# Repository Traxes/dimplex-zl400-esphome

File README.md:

# Dimplex ZL 400 VF – ESPHome controller for Home Assistant

**English** · [Deutsch](README.de.md)

> [!TIP]
> **Want a ready-made one?** I can build the assembled PCB and the 3D-printed enclosure for you – **in any color**, and the case can be adapted to your installation (shape, mounting, cable exits). If you're interested, **[open a request](https://github.com/Traxes/dimplex-zl400-esphome/issues/new?title=Request%3A%20ready-made%20controller&body=Hi%21%20I%20am%20interested%20in%20a%20ready-made%20controller%20%28assembled%20PCB%20%2B%203D-printed%20enclosure%29.%0A%0A-%20Quantity%3A%0A-%20Enclosure%20color%3A%0A-%20Changes%20to%20the%20enclosure%20%28optional%29%3A%0A-%20Shipping%20country%3A%0A%0A%28Please%20do%20not%20post%20your%20address%20or%20phone%20number%20here%20%E2%80%93%20details%20are%20arranged%20privately.%29)**. Please don't post your address or phone number in the issue – details are arranged privately.

<p align="center">
  
  &nbsp;
  
</p>
<p align="center"><sub>Left: installed on a ZL 400 VF, wires to the unit's terminal board. Right: controller v3 in the printed case (lid removed).</sub></p>

A drop-in replacement for the wall control panel (“Bedienelement Typ 1”) of **Dimplex ZL 300 VF / ZL 400 VF** home ventilation units. A Seeed **XIAO ESP32-C6** reads the unit's five 24 V status outputs through optocouplers and “presses” the up/down buttons with optocoupler-driven PNP switches. In Home Assistant the unit shows up as a normal fan with three speeds.

**Highlights**

- Galvanically isolated: the ESP is powered only by USB-C, nothing but optocouplers crosses to the unit's 24 V side.
- Closed-loop control: every key press is verified through the unit's LED outputs; retries with back-off, fault entities for HA.
- KiCad 10 project + ready-to-order JLCPCB files (Gerber, BOM, CPL).
- Snap-fit 3D-printed enclosure without screws, generated by a parametric Fusion 360 script.
- Worst-case analysis, SPICE Monte Carlo and FMEA in [`docs/qa`](docs/qa) (German).

**Status (2026-10-19):** installed and running in a ZL 400 VF. Live test off → 1 → 3 → 2 → off: LED feedback within 3 s for every step, no fault flags.

> [!WARNING]
> The ventilation unit contains mains voltage (230 V). Read the **[safety notes](#safety)** before you open the unit or connect anything. Build at your own risk. This is not a Dimplex product.

## Contents

| Folder | What's inside |
|---|---|
| [`hardware/controller-v3`](hardware/controller-v3) | KiCad project, schematic PDF, JLCPCB fabrication files |
| [`hardware/emulator-lab-v2`](hardware/emulator-lab-v2) | Bench emulator of the unit's terminal board (not built/tested yet) |
| [`firmware`](firmware) | ESPHome config `trax_ha_c6.yaml`, `secrets.example.yaml` |
| [`gehaeuse`](gehaeuse) | Enclosure: STL, 3MF, Bambu Studio project, STEP, Fusion 360 script |
| [`docs`](docs) | QA reports, interactive commissioning checklist, images, dimension sheet |
| [`tools`](tools) | Python scripts used for QA, simulation and fabrication checks |

## Safety

> [!CAUTION]
> Working on the ventilation unit can be **life-threatening**: there is mains voltage (230 V) inside. Read this section completely before you start.

**Electrical**

- Before opening the unit or the terminal compartment, disconnect it from mains **on all poles** (circuit breaker or isolating switch). Secure it against being switched back on and verify that it is dead. Work on mains wiring is for qualified electricians only.
- The controller is designed **only for the unit's 24 V DC control circuit** (PCB3 terminals `+`, `−`, `AUS_x`, `EIN_x`).
  - Never connect any terminal to mains or to another voltage source.
  - The absolute maximum is 30 V; above 27.5 V parts run outside their derating limits.
- Measure `+` to `−` on PCB3 (DC volts) and check every wire against the [wiring diagram](#wiring) before you connect the controller. Swapping `+` and `−` is blocked by diodes; other wiring mistakes are not.
- Use **ferrules** on stranded wires, strip only as much as the terminal needs, and pull-test every wire. A stray strand can short the unit's 24 V supply.
- Leave all other PCB3 terminals untouched. In particular, keep the **RM (smoke detector) bridge** in place: it is a safety shutdown input of the unit.
- Do not connect other loads to the unit's 24 V supply. Its transformer is only rated for a few control panels and sensors (Dimplex manual, table 4.1).

**ESP / USB side**

- Power the XIAO only from a **certified USB power supply** (safety extra-low voltage, CE marked). Never feed it from the unit's 24 V.
- Never connect USB ground or any ESP pin to the unit's wiring. The isolation between the two sides must stay intact.

**Enclosure and location**

- The printed enclosure is **not flame-retardant**: PLA and PETG are not UL 94 V-0. The controller dissipates only milliwatts, but keep it away from heat sources and out of the air stream of electric heater coils.
- PLA softens from about 55 °C; use PETG or ASA for warm locations.
- Install only in dry, frost-free rooms (the same requirements as for the unit itself): no condensation, no outdoor use.
- Close the lid before operation; it protects the terminals against accidental contact.

**Ventilation function**

- Home ventilation protects the building against moisture and mould. Make sure your automations **can never keep the unit off for long periods**, and keep the minimum ventilation required for your building (in Germany, for example, the moisture-protection level of DIN 1946-6).
- If a **fireplace or other combustion appliance** shares the air volume, the safety devices required for that combination (for example a pressure monitor) stay mandatory. This controller does not replace them, and remote control must never override them.
- The unit's own protective functions (frost protection, smoke-detector shutdown, filter alarm) stay active. Do not bypass them.
- A Wi-Fi or firmware fault can leave the unit at its last stage. Watch `control_failed` and `feedback_lost` in Home Assistant; the unit's own display and buttons keep working as a fallback.

**Liability**

- Building and using this is at your own risk. Connecting third-party electronics may affect the warranty of the ventilation unit. The documents come without any guarantee of correctness. This project is not affiliated with Dimplex.

## How it works

| Direction | Circuit |
|---|---|
| Unit → ESP (AUS0–AUS4) | +24 V → 10 kΩ → EL817 LED → AUS. The unit switches AUS to 0 V, exactly like the LEDs of the original panel (≈ 2 mA). Output side: 3.3 V → GPIO with 10 kΩ pull-down. |
| ESP → unit (EIN0/EIN1) | GPIO → 330 Ω → EL817 → pulls the base of an MMBT3906 (22 kΩ); the PNP puts +24 V on EIN through 1 kΩ – like pressing the panel button. 300 ms pulses. |
| Power | ESP from USB-C only (an ESP powered from the unit's 24 V had tripped error E05 at power-up). 24 V side: 1N4148W reverse-polarity protection in + and −, “24V OK” LED. Load on the unit ≈ 1–10 mA. |

## Wiring

Set the unit to **service menu 20 → 21 Bedienelement → “Typ1”**. Terminal assignment follows the Dimplex installation manual ZL 300/400 VF, chapter 4.5.4, fig. 4.13 ([PDF](https://www.dimplex.eu/sites/g/files/emiian586/files/media_import/medias/docus/5/Dimplex_ZL300VF_Montageanweisung-WP_DE_FD9910.pdf)).

> [!IMPORTANT]
> Unlike the original panel, this controller needs the **GND → “−”** wire. Measure between PCB3 “+” and “−” first: the design is rated for 21.6–27 V (see [Known limitations](#known-limitations)).

## Build it

### 1. PCB

1. Upload `hardware/controller-v3/fertigung-jlcpcb/gerbers.zip` to JLCPCB (2 layers, 1.6 mm, 75 × 64 mm), choose PCBA Economic and add the BOM and CPL files. Q1/Q2 (SOT-23) rotation is already corrected by 180° in the CPL. Still check the placement preview.
2. Hand-solder a Seeed **XIAO ESP32-C6** and 5.08 mm screw terminals (2-pin J1, 5-pin J2, 2-pin J3). The XIAO can be soldered directly (the enclosure is dimensioned for that) or plugged into 1×7 socket headers.
3. Commission it step by step with [`docs/Inbetriebnahme_Controller_v3.html`](docs/Inbetriebnahme_Controller_v3.html) (download and open locally; it covers measuring points, multimeter settings and expected values; German).

| Part (assembled by JLCPCB) | LCSC | Qty | Refs |
|---|---|---|---|
| 1N4148W SOD-123 | C81598 | 7 | D1–D5, D7, D8 |
| LED green 0805 | C2297 | 1 | D6 |
| MMBT3906 SOT-23 | C2143 | 2 | Q1, Q2 |
| EL817S SMD-4 | C63268 | 7 | U1–U7 |
| 10 kΩ 0805 | C17414 | 14 | R1–R10, R15, R16, R18, R19 |
| 22 kΩ 0805 | C17560 | 3 | R13, R14, R17 |
| 330 Ω 0805 | C17630 | 2 | R11, R12 |
| 1 kΩ 0805 | C17513 | 2 | R20, R21 |

### 2. Firmware

1. Copy `firmware/secrets.example.yaml` to `secrets.yaml` and fill it in. Never commit it, it is in `.gitignore`.
2. Add `trax_ha_c6.yaml` in the ESPHome dashboard and flash it over USB. If you get “Failed to connect”, hold the **B (BOOT)** button next to the USB socket while plugging in the cable. After that, OTA works.
3. Adopt the device in Home Assistant (ESPHome integration).

| Entity | Purpose |
|---|---|
| `fan.<device>_ventilation` | 3 speeds: 33 / 66 / 100 %, off = unit off |
| `sensor.<device>_ventilation_level` | Actual stage 0–3 from the unit's LEDs |
| `sensor.<device>_ventilation_status` | OK / adjusting / fault text |
| `binary_sensor.<device>_ventilation_auto`, `…_error` | Auto mode, fault/filter LED |
| `…_control_failed`, `…_feedback_lost`, `…_stuck_key_suspected` | Diagnostics |
| `sensor.<device>_ventilation_uncommanded_changes` | Stage changes not caused by HA |
| `button.<device>_ventilation_clear_faults` | Reset diagnostics |

#### In Home Assistant

<p align="center"><sub>Device page with the fan dialog. The activity log shows a real command from an automation: fan on at 22:10:00, LED feedback for stage 1 in the same second, status “OK” at 22:10:02.</sub></p>

- The fan dialog offers **Off / Low / Medium / High**: stages 0–3, 0 / 33 / 66 / 100 %.
- The status sensor uses German texts:

| Status | Meaning |
|---|---|
| `OK` | Idle, stage confirmed by the unit's LEDs |
| `Stellt ein: 1 → 2` | Adjusting from stage 1 to 2 |
| `Aus (oder 24 V fehlt)` | Unit is off – or there is no 24 V / no LED signal at all |
| `Gestört/unbekannt – keine Rückmeldung` | A key press caused no LED change (check 24 V, wiring, EIN) |
| `Steuerung fehlgeschlagen` | Target not reached after all retries |
| `Verdacht Dauerdruck – Hardware prüfen (T2)` | Stage moved against the pressed direction – possible stuck key |
| `Start` | Booting; key presses are blocked until the first sync |

Tested with ESPHome 2026.9.1 on a XIAO ESP32-C6.

**Control logic:** A requested speed becomes single key presses (300 ms pulse, 700 ms pause). After each press the firmware waits up to 2 s for the stage LEDs to change. If they don't, it retries with back-off (1/2/4/4 s, max. 10 presses). On boot the entity syncs to the real stage without pressing anything.

```yaml
# Example automation action
action: fan.set_percentage
target:
  entity_id: fan.trax_ha_c6_ventilation
data:
  percentage: 66   # 33 = stage 1, 66 = stage 2, 100 = stage 3; use fan.turn_off for off
```

LED feedback is immediate. The fans themselves need about 30–70 s to reach their speed.

### 3. Enclosure

- **Size:** 80.7 × 69.8 × 24.1 mm, 95.8 mm long including the two wall-mounting tabs (slots for Ø 4 screws).
- **No hardware needed:** pins on the bosses locate the PCB, four hold-downs in the lid clamp it, and the lid snaps into four windows. To open it, push each hook inwards through its window with a small screwdriver.
- **Openings:** nine labelled wire holes (Ø 3.9 mm, aligned with the terminal entries), a USB-C opening, pin holes for RESET/BOOT (paper clip) and a light pipe for “24V OK”.
- **Printing** (tested on a Bambu Lab P2S, PLA): 0.2 mm layers, 4 walls, 4 bottom layers, 15 % infill, no supports, lid printed top-down. About 1 h 25 min and 49 g. Use PETG for warm locations.
- **Files:**
  - `CentralVentilationCase_BambuStudio_P2S_PLA.3mf`: ready-to-print Bambu Studio project
  - `…_Geometrie.3mf`: for other slicers
  - single STL files
  - STEP assembly with a PCB dummy
- **Modify:** [`gehaeuse/fusion/gehaeuse_fusion.py`](gehaeuse/fusion/gehaeuse_fusion.py) rebuilds the whole model in Fusion 360 via the API. All dimensions are at the top of the script; the measurements come from the [dimension sheet](docs/bilder/massblatt_controller_v3.png).

## Emulator (optional)

Bench replica of the unit's terminal board: DIP switches pull AUS0–4 to 0 V, LEDs show EIN0/EIN1. **Not manufactured or tested yet.** LED polarities in the assembly preview are unverified.

## Known limitations

Details are in [`docs/qa/QA_Verifikation_2026-10-15.md`](docs/qa/QA_Verifikation_2026-10-15.md) (German).

- **Supply voltage:** designed to EEE-INST-002 derating for 21.6–30 V. Above **27.5 V** the output optocouplers U6/U7 exceed the derating limit (absolute max 35 V), and above ≈ 29 V so do R1–R5. Spikes on the 24 V line have not been measured.
- **EIN input current** of the unit has not been measured. It decides whether R20/R21 = 1 kΩ is optimal (up to 4 mA the unit still sees ≥ 19 V).
- **Short circuit on EIN** is tolerable for the pulse length only: a permanent short would put 0.5 W into R20/R21, which are rated 0.125 W.
- **A stuck key is not single-fault safe:** a shorted Q1/Q2 or U6/U7 would hold a button down. The firmware only detects it indirectly (`stuck_key_suspected`).

## Tools

`tools/qa` and `tools/verifikation` contain the scripts that generated and verified schematic and layout:
- KiCad 10 Python
- ngspice via the KiCad DLL
- gerbonara / shapely

Local paths are replaced by `<PROJEKT>` / `<HOME>`; adjust them before running.

## License

[MIT](LICENSE): free to use, build, modify and share, also commercially, as long as the license notice is kept. Symbols and footprints embedded in the KiCad files come from the KiCad libraries (CC-BY-SA 4.0 with the KiCad design exception) and do not restrict your own boards.

## Disclaimer

Dimplex and ZL 400 VF are trademarks of Glen Dimplex Deutschland GmbH; XIAO is a trademark of Seeed Studio. This project is not affiliated with or endorsed by either company.

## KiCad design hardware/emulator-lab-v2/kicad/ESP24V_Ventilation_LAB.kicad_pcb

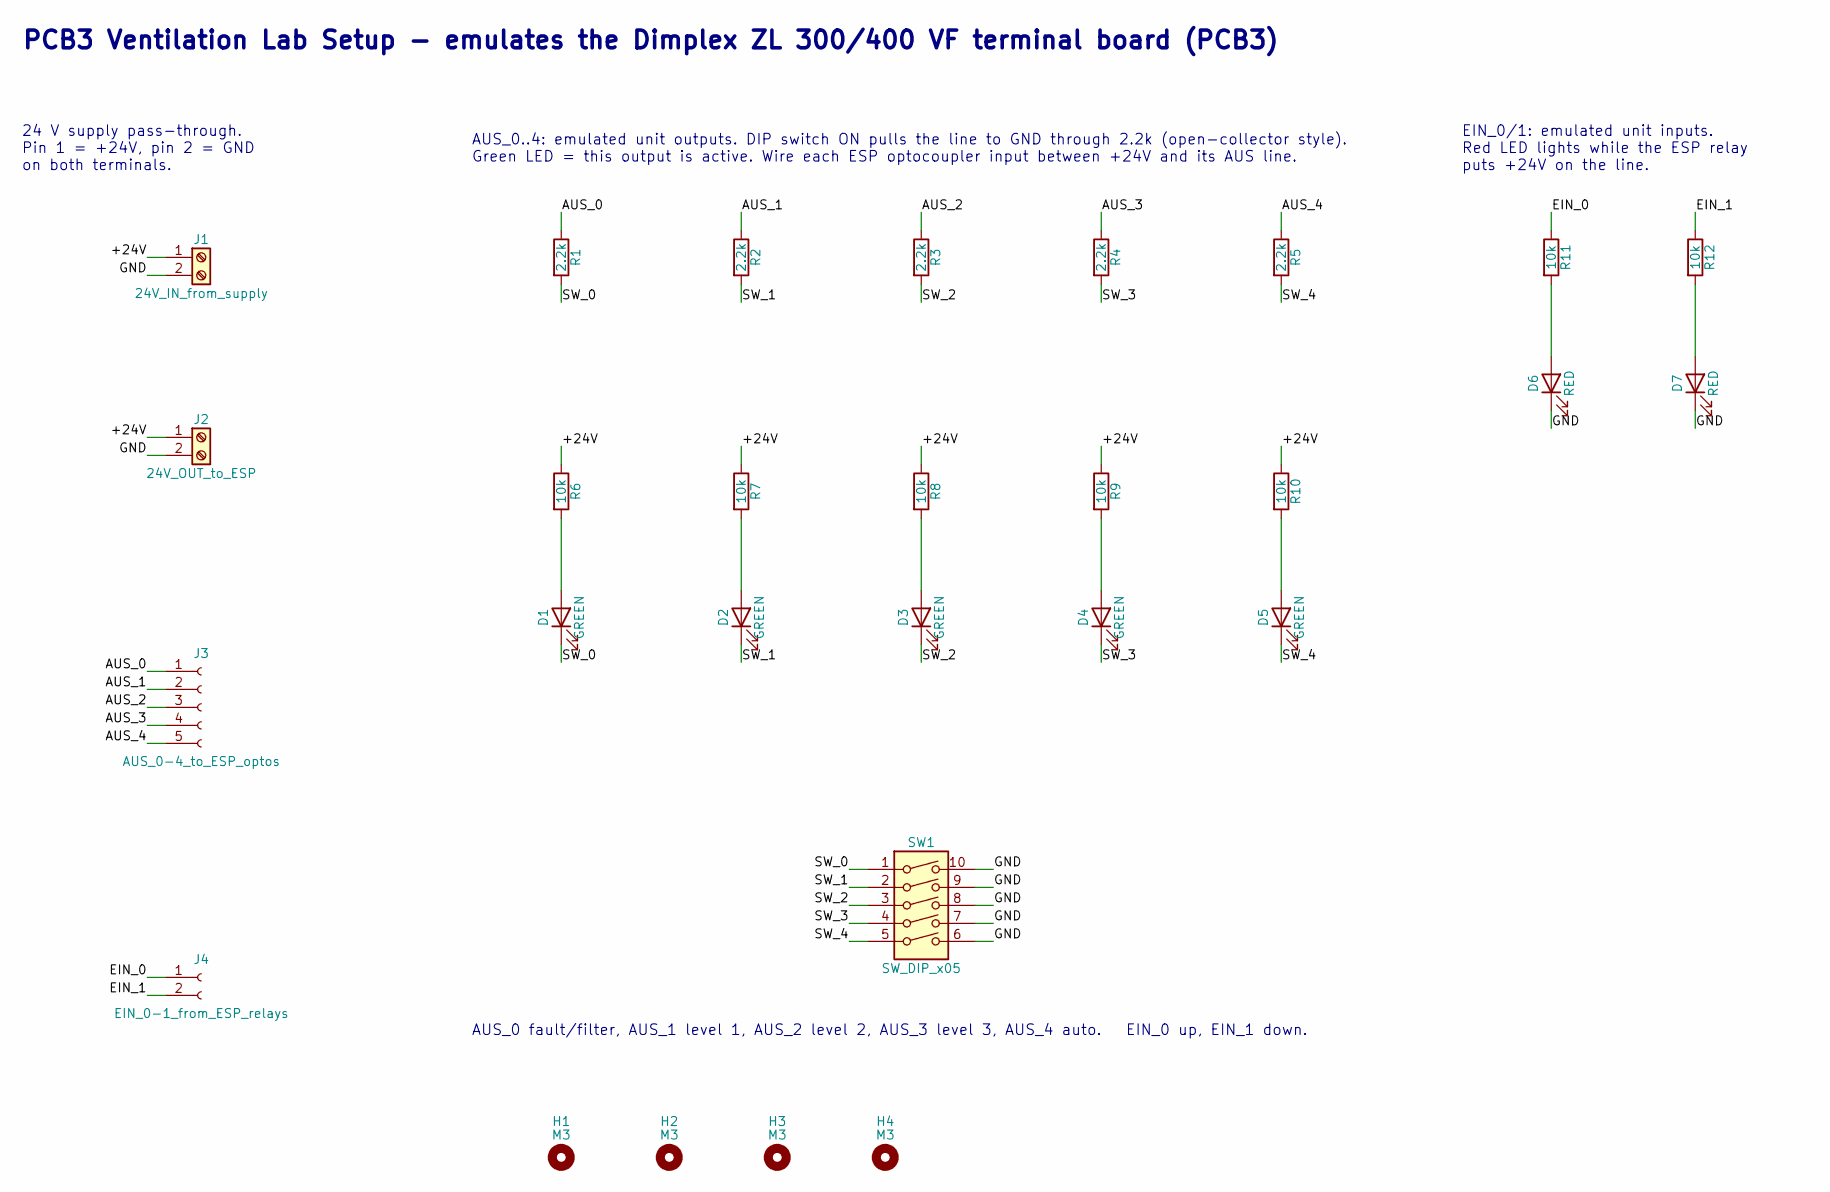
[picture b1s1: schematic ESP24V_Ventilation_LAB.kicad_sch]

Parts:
D1, D2, D3, D4, D5: GREEN; LED_0805_2012Metric; LCSC C2297
D6, D7: RED; LED_0805_2012Metric; LCSC C84256
H1, H2, H3, H4: M3; MountingHole_3.2mm_M3
J1: 24V_IN_from_supply; TerminalBlock_Phoenix_MKDS-1,5-2-5.08_1x02_P5.08mm_Horizont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
J2: 24V_OUT_to_ESP; TerminalBlock_Phoenix_MKDS-1,5-2-5.08_1x02_P5.08mm_Horizont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
J3: AUS_0-4_to_ESP_optos; PinSocket_1x05_P2.54mm_Vertical
J4: EIN_0-1_from_ESP_relays; PinSocket_1x02_P2.54mm_Vertical
R1, R2, R3, R4, R5: 2.2k; R_0805_2012Metric; LCSC C17520
R6, R7, R8, R9, R10, R11, R12: 10k; R_0805_2012Metric; LCSC C17414
SW1: SW_DIP_x05; SW_DIP_SPSTx05_Slide_9.78x14.88mm_W7.62mm_P2.54mm

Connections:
/+24V: J1.1, J2.1, R6.1, R7.1, R8.1, R9.1, R10.1
/AUS_0: J3.1, R1.1
/AUS_1: J3.2, R2.1
/AUS_2: J3.3, R3.1
/AUS_3: J3.4, R4.1
/AUS_4: J3.5, R5.1
/EIN_0: J4.1, R11.1
/EIN_1: J4.2, R12.1
/GND: D6.1 (K), D7.1 (K), J1.2, J2.2, SW1.6, SW1.7, SW1.8, SW1.9, SW1.10
/SW_0: D1.1 (K), R1.2, SW1.1
/SW_1: D2.1 (K), R2.2, SW1.2
/SW_2: D3.1 (K), R3.2, SW1.3
/SW_3: D4.1 (K), R4.2, SW1.4
/SW_4: D5.1 (K), R5.2, SW1.5
unnamed: D1.2 (A), R6.2
unnamed: D2.2 (A), R7.2
unnamed: D3.2 (A), R8.2
unnamed: D4.2 (A), R9.2
unnamed: D5.2 (A), R10.2
unnamed: D6.2 (A), R11.2
unnamed: D7.2 (A), R12.2

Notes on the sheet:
PCB3 Ventilation Lab Setup - emulates the Dimplex ZL 300/400 VF terminal board (PCB3)
AUS_0..4: emulated unit outputs. DIP switch ON pulls the line to GND through 2.2k (open-collector style). Green LED = this output is active. Wire each ESP optocoupler input between +24V and its AUS line.
EIN_0/1: emulated unit inputs. Red LED lights while the ESP relay puts +24V on the line.
AUS_0 fault/filter, AUS_1 level 1, AUS_2 level 2, AUS_3 level 3, AUS_4 auto. EIN_0 up, EIN_1 down.
24 V supply pass-through. Pin 1 = +24V, pin 2 = GND on both terminals.

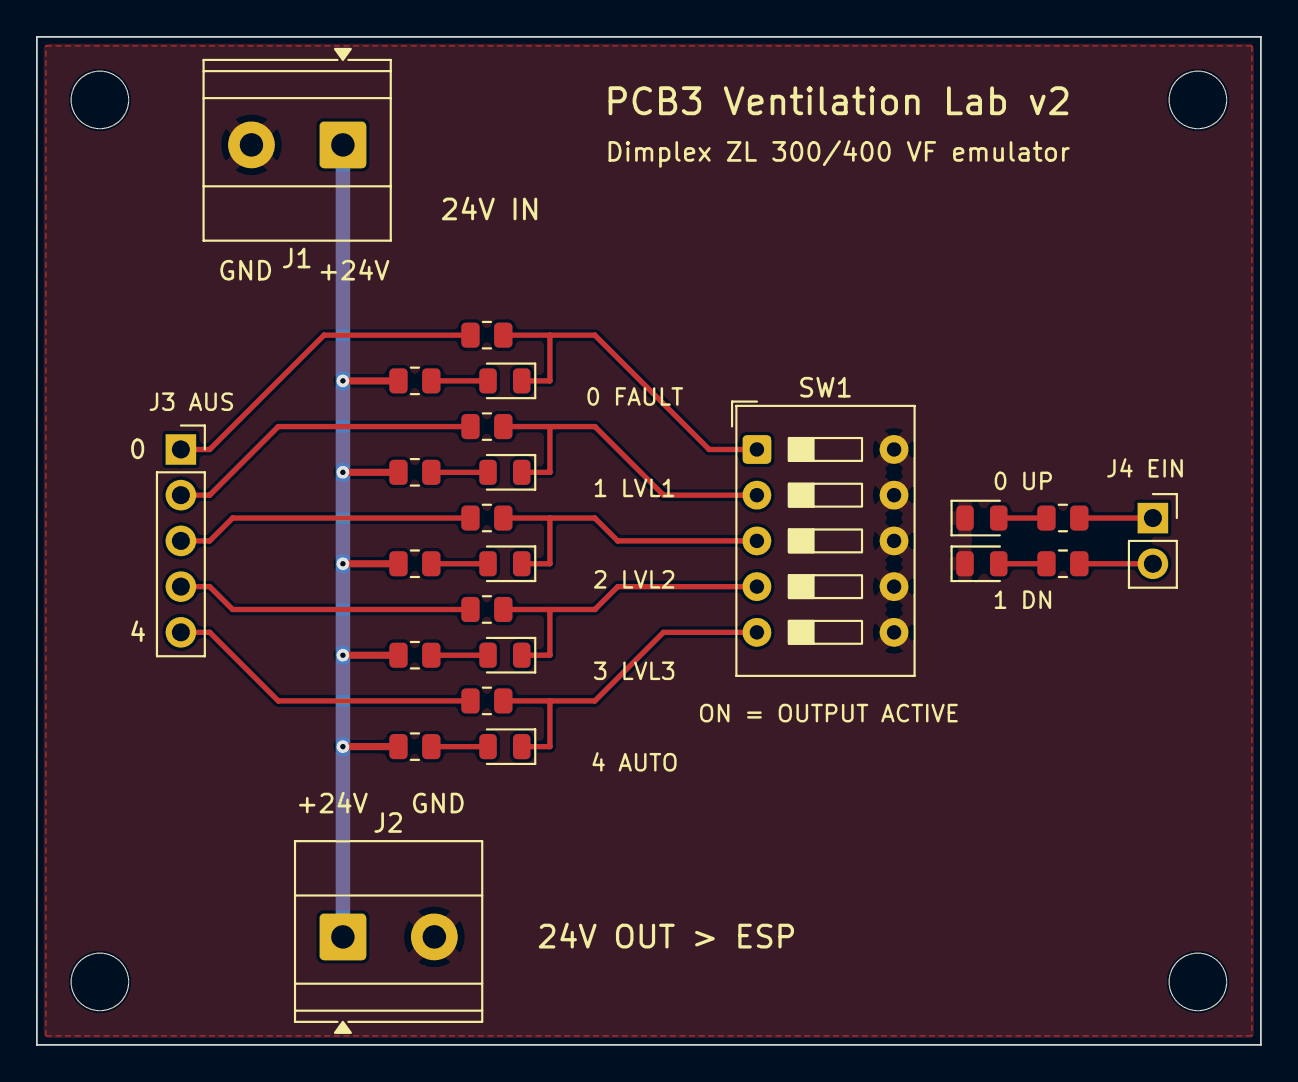
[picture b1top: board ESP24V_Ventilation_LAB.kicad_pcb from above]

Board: 2 copper layers, 68.0 x 56.0 mm, 28 parts (0 on the bottom side), 21 nets.

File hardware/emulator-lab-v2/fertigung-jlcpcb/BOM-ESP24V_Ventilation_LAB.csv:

Comment,Designator,Footprint,LCSC Part #
GREEN,"D1,D2,D3,D4,D5",LED_SMD:LED_0805_2012Metric,C2297
RED,"D6,D7",LED_SMD:LED_0805_2012Metric,C84256
2.2k,"R1,R2,R3,R4,R5",Resistor_SMD:R_0805_2012Metric,C17520
10k,"R6,R7,R8,R9,R10,R11,R12",Resistor_SMD:R_0805_2012Metric,C17414

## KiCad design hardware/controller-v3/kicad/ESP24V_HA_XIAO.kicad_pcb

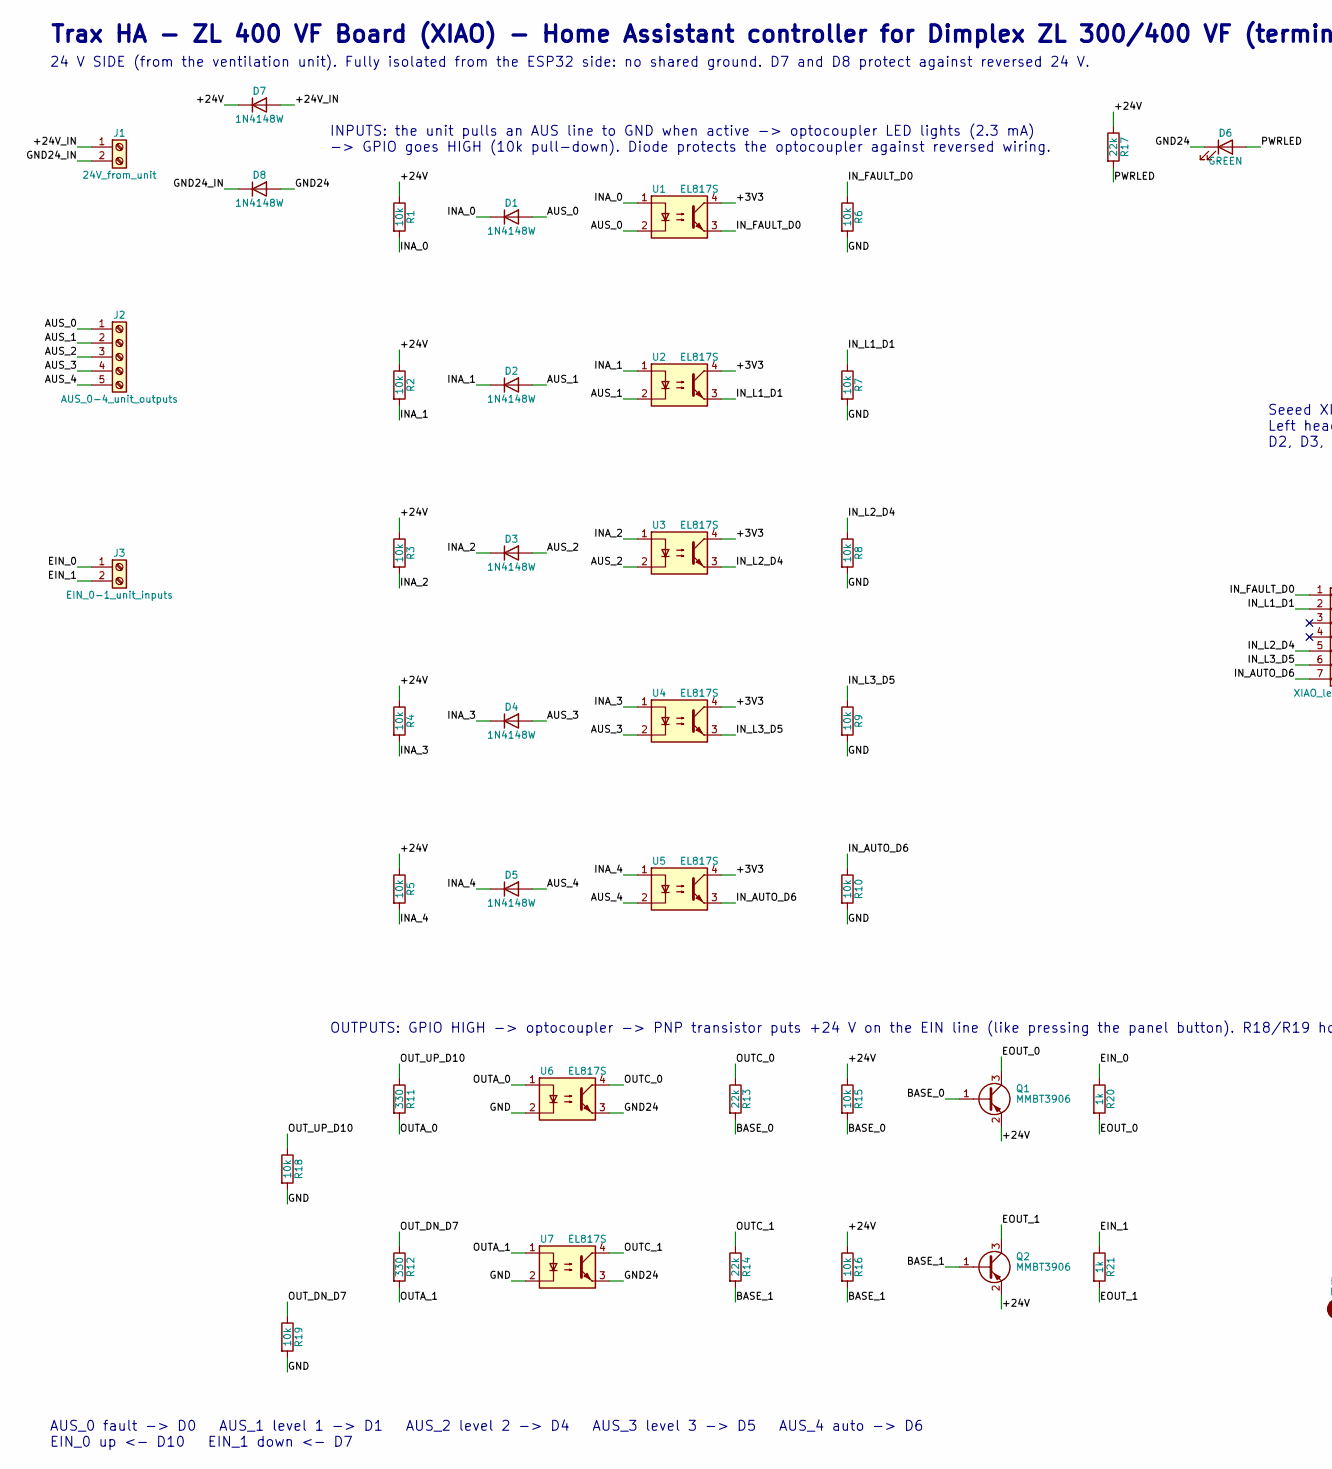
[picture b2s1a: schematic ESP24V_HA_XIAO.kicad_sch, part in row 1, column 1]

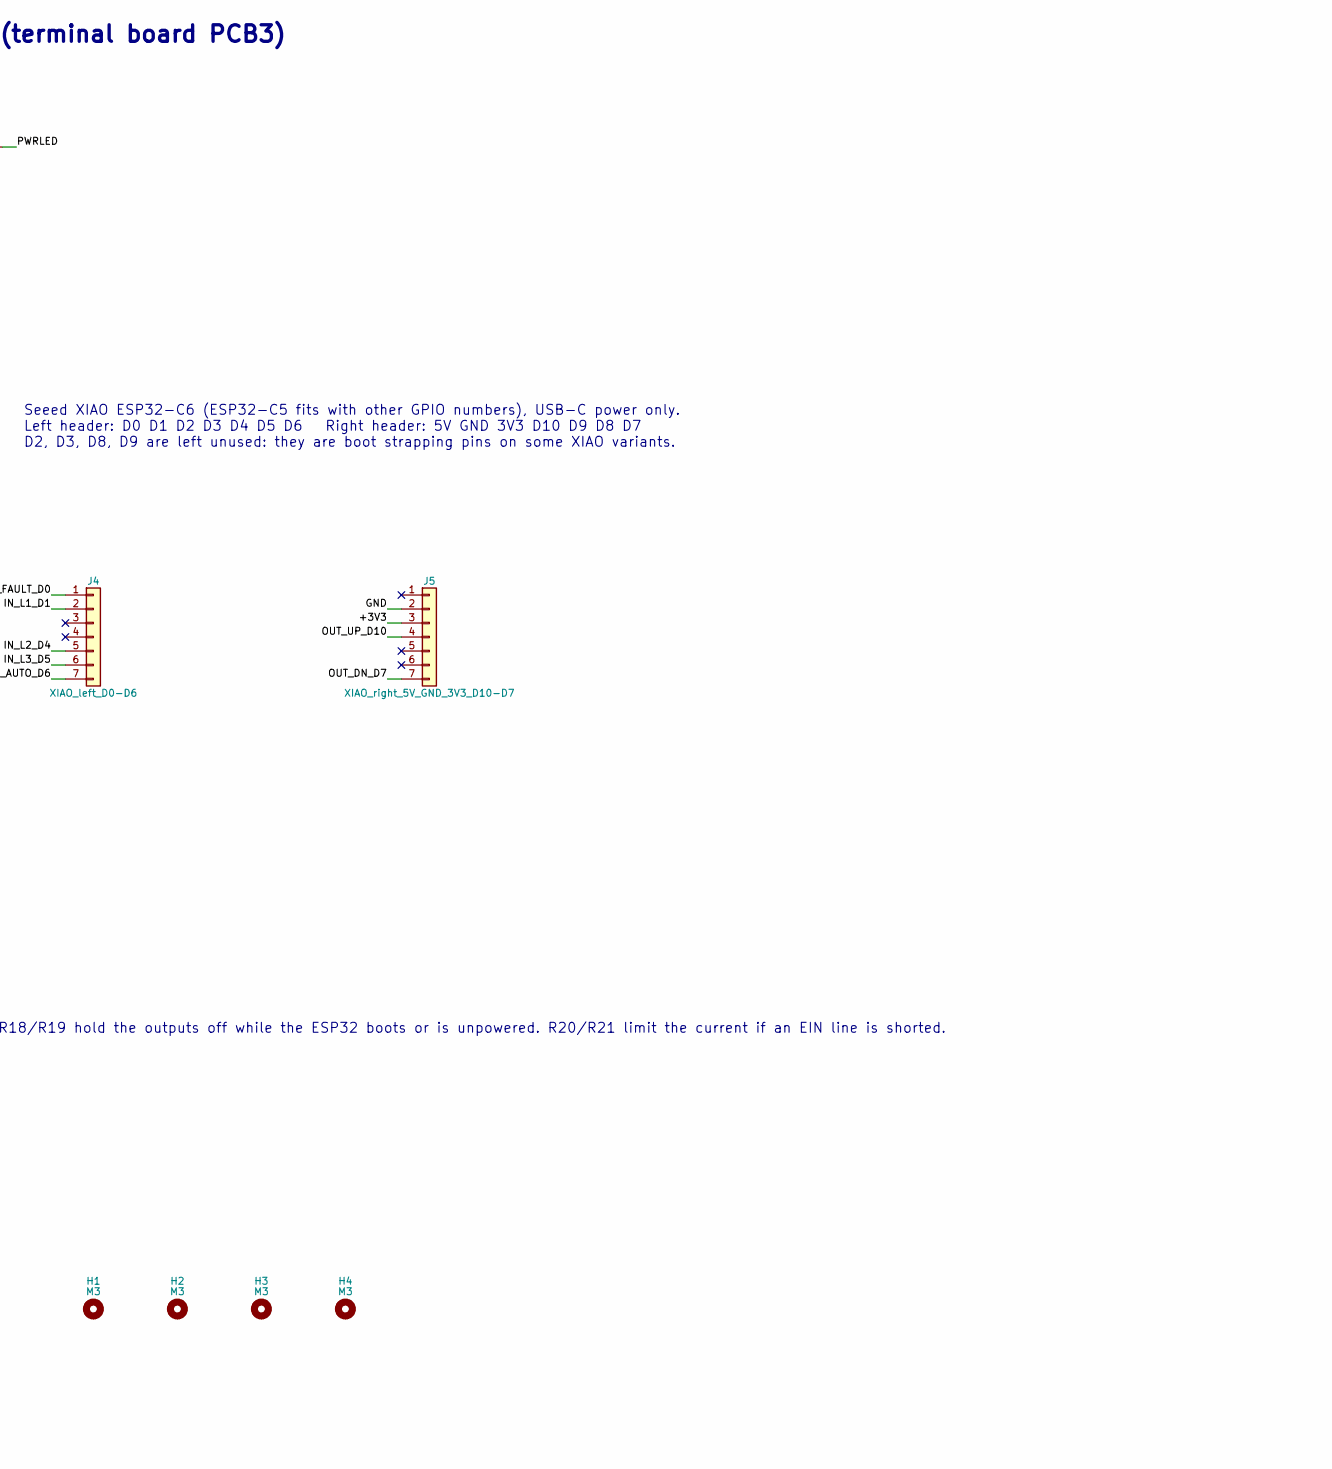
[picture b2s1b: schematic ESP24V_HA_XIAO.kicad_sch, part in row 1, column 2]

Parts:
D1, D2, D3, D4, D5, D7, D8: 1N4148W; D_SOD-123; LCSC C81598
D6: GREEN; LED_0805_2012Metric; LCSC C2297
H1, H2, H3, H4: M3; MountingHole_3.2mm_M3
J1: 24V_from_unit; TerminalBlock_Phoenix_MKDS-1,5-2-5.08_1x02_P5.08mm_Horizont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
J2: AUS_0-4_unit_outputs; TerminalBlock_Phoenix_MKDS-1,5-5-5.08_1x05_P5.08mm_Horizont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
J3: EIN_0-1_unit_inputs; TerminalBlock_Phoenix_MKDS-1,5-2-5.08_1x02_P5.08mm_Horizont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
J4: XIAO_left_D0-D6; PinSocket_1x07_P2.54mm_Vertical
J5: XIAO_right_5V_GND_3V3_D10-D7; PinSocket_1x07_P2.54mm_Vertical
Q1, Q2: MMBT3906; SOT-23; LCSC C2143
R1, R2, R3, R4, R5, R6, R7, R8, R9, R10, R15, R16, R18, R19: 10k; R_0805_2012Metric; LCSC C17414
R11, R12: 330; R_0805_2012Metric; LCSC C17630
R13, R14, R17: 22k; R_0805_2012Metric; LCSC C17560
R20, R21: 1k; R_0805_2012Metric; LCSC C17513
U1, U2, U3, U4, U5, U6, U7: EL817S; SMDIP-4_W9.53mm; LCSC C63268

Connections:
/+3V3: J5.3, U1.4, U2.4, U3.4, U4.4, U5.4
/+24V: D7.1 (K), Q1.2 (E), Q2.2 (E), R1.1, R2.1, R3.1, R4.1, R5.1, R15.1, R16.1, R17.1
/+24V_IN: D7.2 (A), J1.1
/AUS_0: D1.2 (A), J2.1, U1.2
/AUS_1: D2.2 (A), J2.2, U2.2
/AUS_2: D3.2 (A), J2.3, U3.2
/AUS_3: D4.2 (A), J2.4, U4.2
/AUS_4: D5.2 (A), J2.5, U5.2
/BASE_0: Q1.1 (B), R13.2, R15.2
/BASE_1: Q2.1 (B), R14.2, R16.2
/EIN_0: J3.1, R20.1
/EIN_1: J3.2, R21.1
/EOUT_0: Q1.3 (C), R20.2
/EOUT_1: Q2.3 (C), R21.2
/GND: J5.2, R6.2, R7.2, R8.2, R9.2, R10.2, R18.2, R19.2, U6.2, U7.2
/GND24: D6.1 (K), D8.2 (A), U6.3, U7.3
/GND24_IN: D8.1 (K), J1.2
/INA_0: D1.1 (K), R1.2, U1.1
/INA_1: D2.1 (K), R2.2, U2.1
/INA_2: D3.1 (K), R3.2, U3.1
/INA_3: D4.1 (K), R4.2, U4.1
/INA_4: D5.1 (K), R5.2, U5.1
/IN_AUTO_D6: J4.7, R10.1, U5.3
/IN_FAULT_D0: J4.1, R6.1, U1.3
/IN_L1_D1: J4.2, R7.1, U2.3
/IN_L2_D4: J4.5, R8.1, U3.3
/IN_L3_D5: J4.6, R9.1, U4.3
/OUTA_0: R11.2, U6.1
/OUTA_1: R12.2, U7.1
/OUTC_0: R13.1, U6.4
/OUTC_1: R14.1, U7.4
/OUT_DN_D7: J5.7, R12.1, R19.1
/OUT_UP_D10: J5.4, R11.1, R18.1
/PWRLED: D6.2 (A), R17.2

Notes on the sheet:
Trax HA - ZL 400 VF Board (XIAO) - Home Assistant controller for Dimplex ZL 300/400 VF (terminal board PCB3)
24 V SIDE (from the ventilation unit). Fully isolated from the ESP32 side: no shared ground. D7 and D8 protect against reversed 24 V.
INPUTS: the unit pulls an AUS line to GND when active -> optocoupler LED lights (2.3 mA) -> GPIO goes HIGH (10k pull-down). Diode protects the optocoupler against reversed wiring.
OUTPUTS: GPIO HIGH -> optocoupler -> PNP transistor puts +24 V on the EIN line (like pressing the panel button). R18/R19 hold the outputs off while the ESP32 boots or is unpowered. R20/R21 limit the current if an EIN line is shorted.
Seeed XIAO ESP32-C6 (ESP32-C5 fits with other GPIO numbers), USB-C power only. Left header: D0 D1 D2 D3 D4 D5 D6 Right header: 5V GND 3V3 D10 D9 D8 D7 D2, D3, D8, D9 are left unused: they are boot strapping pins on some XIAO variants.
AUS_0 fault -> D0 AUS_1 level 1 -> D1 AUS_2 level 2 -> D4 AUS_3 level 3 -> D5 AUS_4 auto -> D6 EIN_0 up <- D10 EIN_1 down <- D7

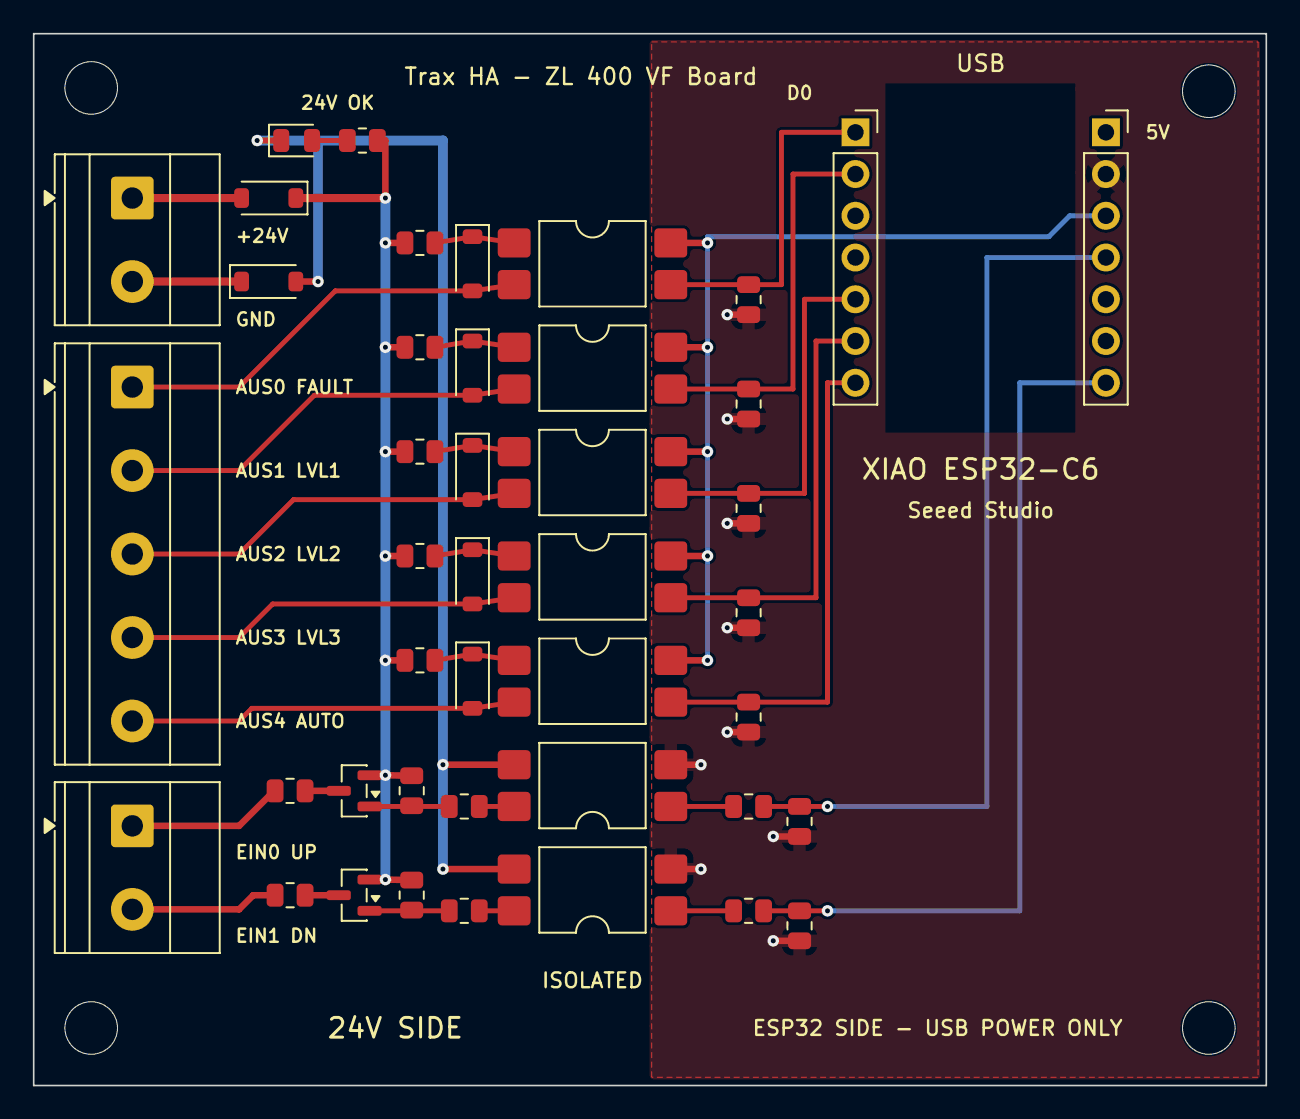
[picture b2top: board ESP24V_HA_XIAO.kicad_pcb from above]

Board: 2 copper layers, 75.0 x 64.0 mm, 47 parts (0 on the bottom side), 34 nets.

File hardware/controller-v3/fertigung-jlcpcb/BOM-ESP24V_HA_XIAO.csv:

Comment,Designator,Footprint,LCSC Part #
1N4148W,"D1,D2,D3,D4,D5,D7,D8",Diode_SMD:D_SOD-123,C81598
GREEN,D6,LED_SMD:LED_0805_2012Metric,C2297
MMBT3906,"Q1,Q2",Package_TO_SOT_SMD:SOT-23,C2143
10k,"R1,R2,R3,R4,R5,R6,R7,R8,R9,R10,R15,R16,R18,R19",Resistor_SMD:R_0805_2012Metric,C17414
330,"R11,R12",Resistor_SMD:R_0805_2012Metric,C17630
22k,"R13,R14,R17",Resistor_SMD:R_0805_2012Metric,C17560
1k,"R20,R21",Resistor_SMD:R_0805_2012Metric,C17513
EL817S,"U1,U2,U3,U4,U5,U6,U7",Package_DIP:SMDIP-4_W9.53mm,C63268

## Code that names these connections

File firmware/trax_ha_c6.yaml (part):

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# 3 Stufen) stammt aus perfkitchenvent.yaml (ESP32-DevKit mit Relais).
#
# Pinbelegung:
#   AUS_0 Fehler/Filter   D0   GPIO0    Eingang, HIGH = aktiv
#   AUS_1 Stufe 1         D1   GPIO1    Eingang
#   AUS_2 Stufe 2         D4   GPIO22   Eingang
#   AUS_3 Stufe 3         D5   GPIO23   Eingang
#   AUS_4 Automatik       D6   GPIO16   Eingang (UART0 TX → Logger auf USB)
#   EIN_0 Taste hoch      D10  GPIO18   Ausgang, HIGH = Druck
#   EIN_1 Taste runter    D7   GPIO17   Ausgang (UART0 RX)
#   RF-Schalter-Versorgung     GPIO3    LOW = an (Seeed Q3/R21), F1
#   Antennenwahl               GPIO14   LOW = interne Antenne
#
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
